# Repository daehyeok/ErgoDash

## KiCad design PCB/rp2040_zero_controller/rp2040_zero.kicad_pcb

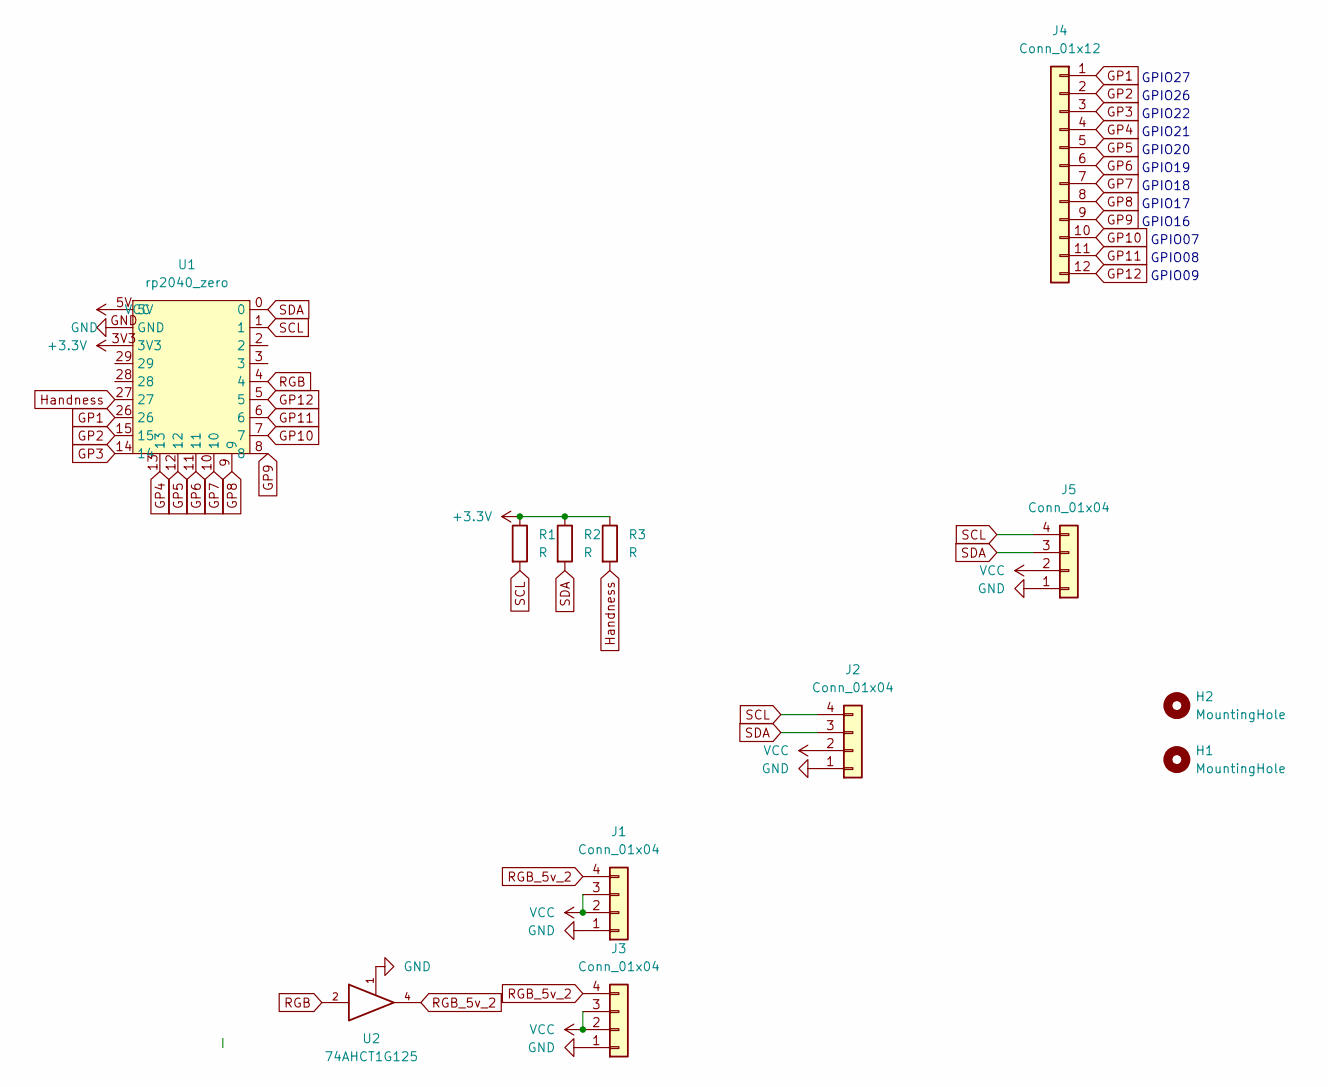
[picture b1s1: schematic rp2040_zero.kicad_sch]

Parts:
H1, H2: MountingHole; MountingHole_2.1mm
J1, J2, J3, J5: Conn_01x04; JST_SH_SM04B-SRSS-TB_1x04-1MP_P1.00mm_Horizontal
J4: Conn_01x12; Molex_200528-0120_1x12-1MP_P1.00mm_Horizontal
R1, R2, R3: R; R_1206_3216Metric_Pad1.30x1.75mm_HandSolder
U1: rp2040_zero; RPi_Pico_C
U2: 74AHCT1G125; SOT-23-5_HandSoldering

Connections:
+3V3: R1.1, R2.1, R3.1, U1.3V3
GND: J1.1, J2.1, J3.1, J5.1, U1.GND, U2.1, U2.3 (GND)
GP1: J4.1, U1.26
GP2: J4.2, U1.15
GP3: J4.3, U1.14
GP4: J4.4, U1.13
GP5: J4.5, U1.12
GP6: J4.6, U1.11
GP7: J4.7, U1.10
GP8: J4.8, U1.9
GP9: J4.9, U1.8
GP10: J4.10, U1.7
GP11: J4.11, U1.6
GP12: J4.12, U1.5
Handness: R3.2, U1.27
RGB: U1.4, U2.2
RGB_5v_2: J1.4, J3.4, U2.4
SCL: J2.4, J5.4, R1.2, U1.1
SDA: J2.3, J5.3, R2.2, U1.0
VCC: J1.2, J1.3, J2.2, J3.2, J3.3, J5.2, U1.5V, U2.5 (VCC)

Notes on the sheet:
GPIO27
GPIO08
GPIO22
GPIO18
GPIO21
GPIO20
GPIO17
GPIO16
GPIO26
GPIO19
GPIO07
GPIO09

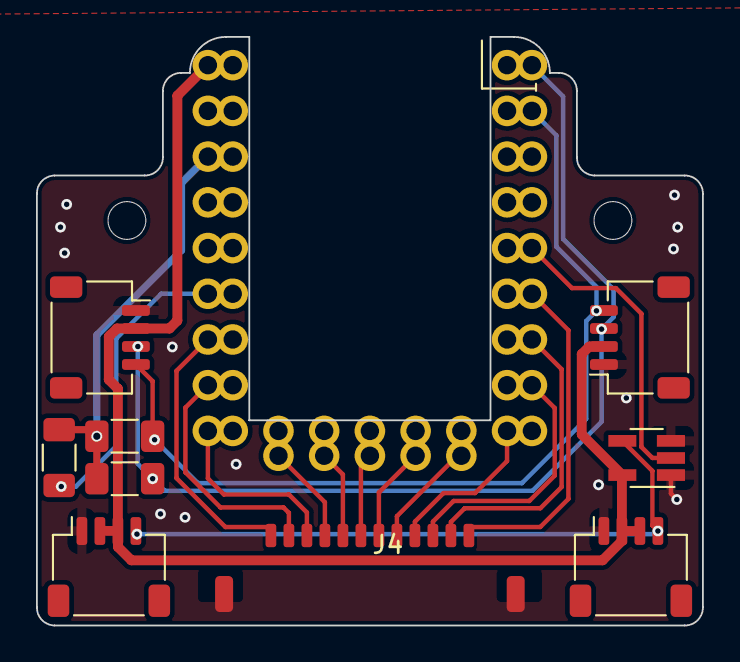
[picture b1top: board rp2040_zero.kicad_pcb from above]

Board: 2 copper layers, 37.0 x 32.7 mm, 12 parts (0 on the bottom side), 20 nets.

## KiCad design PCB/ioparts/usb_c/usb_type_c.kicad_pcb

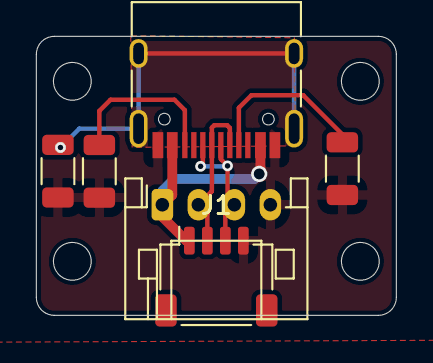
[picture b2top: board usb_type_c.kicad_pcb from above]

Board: 2 copper layers, 20.0 x 15.5 mm, 10 parts (0 on the bottom side), 7 nets.

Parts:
H1, H2, H3, H4: MountingHole; MountingHole_2.1mm
J1: Conn_01x04; JST_SH_SM04B-SRSS-TB_1x04-1MP_P1.00mm_Horizontal
J2: USB_C_Receptacle_USB2.0; USB_C_Receptacle_HRO_TYPE-C-31-M-12
J4: Conn_01x04; JST_PH_S4B-PH-K_1x04_P2.00mm_Horizontal
R1, R2: 5.1K; R_1206_3216Metric
R3: 0; R_1206_3216Metric

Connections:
DM_C: J1.2, J2.A7 (D-), J2.B7 (D-), J4.2
DP_C: J1.3, J2.A6 (D+), J2.B6 (D+), J4.3
GND: J1.4, J2.A1 (GND), J2.A12 (GND), J2.B1 (GND), J2.B12 (GND), J4.4, R1.2, R2.2, R3.2
unnamed: J2.A5 (CC1), R1.1
unnamed: J2.B5 (CC2), R2.1
SHIELD: J2.S1 (SHIELD), R3.1
VBUS_C: J1.1, J2.A4 (VBUS), J2.A9 (VBUS), J2.B4 (VBUS), J2.B9 (VBUS), J4.1

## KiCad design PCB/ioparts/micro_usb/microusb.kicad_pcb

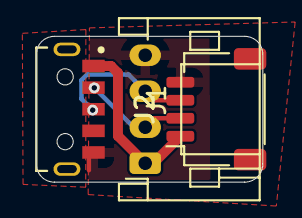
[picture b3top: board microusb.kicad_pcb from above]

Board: 2 copper layers, 12.6 x 8.1 mm, 3 parts (0 on the bottom side), 4 nets.

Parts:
J1: USB_B_Micro; HRO_U-G-M5WS-W-01
J2: Conn_01x04; JST_SH_SM04B-SRSS-TB_1x04-1MP_P1.00mm_Horizontal
J3: Conn_01x04; JST_PH_S4B-PH-K_1x04_P2.00mm_Horizontal

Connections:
DM_MICRO: J1.2 (D-), J2.2, J3.2
DP_MICRO: J1.3 (D+), J2.3, J3.3
GND1: J1.5 (GND), J2.4, J3.4
VBUS: J1.1 (VBUS), J2.1, J3.1

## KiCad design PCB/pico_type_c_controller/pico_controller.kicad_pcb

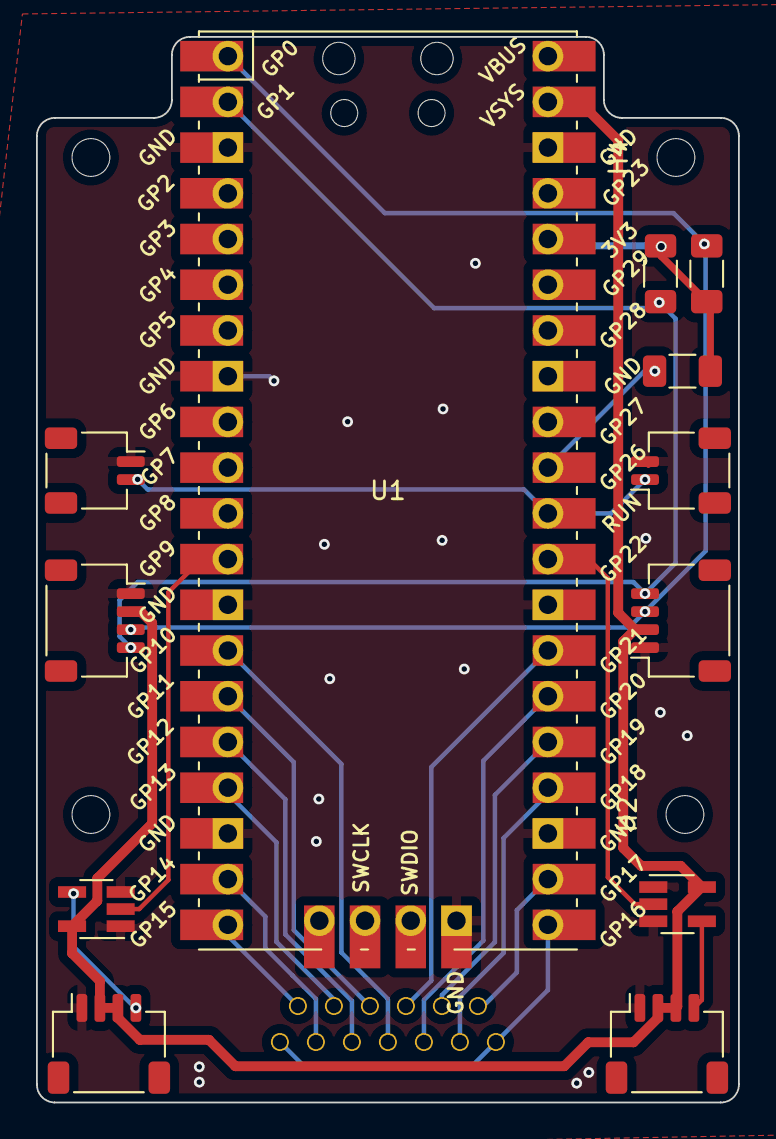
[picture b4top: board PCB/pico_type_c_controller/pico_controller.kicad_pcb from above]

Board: 2 copper layers, 39.0 x 59.2 mm, 17 parts (1 on the bottom side), 23 nets.

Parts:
H1, H2, H3, H4: MountingHole; MountingHole_2.1mm
J1, J2, J3, J5: Conn_01x04; JST_SH_SM04B-SRSS-TB_1x04-1MP_P1.00mm_Horizontal
J4: Conn_01x12; HDGC_1.0K-J-12PW
J6, J7: Conn_01x02; JST_SH_SM02B-SRSS-TB_1x02-1MP_P1.00mm_Horizontal
R1, R2, R3: R; R_1206_3216Metric_Pad1.30x1.75mm_HandSolder
U1: Pico; RPi_Pico_C
U2, U3: 74AHCT1G125; SOT-23-5_HandSoldering

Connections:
+3V3: R1.1, R2.1, R3.2, U1.36 (3V3)
GND: J1.1, J2.1, J3.1, J5.1, J6.2, J7.1, U1.3 (GND), U1.8 (GND), U1.13 (GND), U1.18 (GND), U1.23 (GND), U1.28 (GND), U1.38 (GND), U1.42 (GND), U2.1, U2.3 (GND), U3.1, U3.3 (GND)
GP1: J4.1, U1.20 (GPIO15)
GP2: J4.2, U1.19 (GPIO14)
GP3: J4.3, U1.17 (GPIO13)
GP4: J4.4, U1.16 (GPIO12)
GP5: J4.5, U1.15 (GPIO11)
GP6: J4.6, U1.14 (GPIO10)
GP7: J4.7, U1.27 (GPIO21)
GP8: J4.8, U1.26 (GPIO20)
GP9: J4.9, U1.25 (GPIO19)
GP10: J4.10, U1.24 (GPIO18)
GP11: J4.11, U1.22 (GPIO17)
GP12: J4.12, U1.21 (GPIO16)
Handness: R3.1, U1.31 (GPIO26_ADC0)
RGB: U1.29 (GPIO22), U3.2
RGB2: U1.12 (GPIO9), U2.2
RGB_5v: J2.4, U3.4
RGB_5v_2: J3.4, U2.4
RUN: J6.1, J7.2, U1.30 (RUN)
SCL: J1.4, J5.4, R2.2, U1.2 (GPIO1)
SDA: J1.3, J5.3, R1.2, U1.1 (GPIO0)
VCC: J1.2, J2.2, J2.3, J3.2, J3.3, J5.2, U1.39 (VSYS), U2.5 (VCC), U3.5 (VCC)

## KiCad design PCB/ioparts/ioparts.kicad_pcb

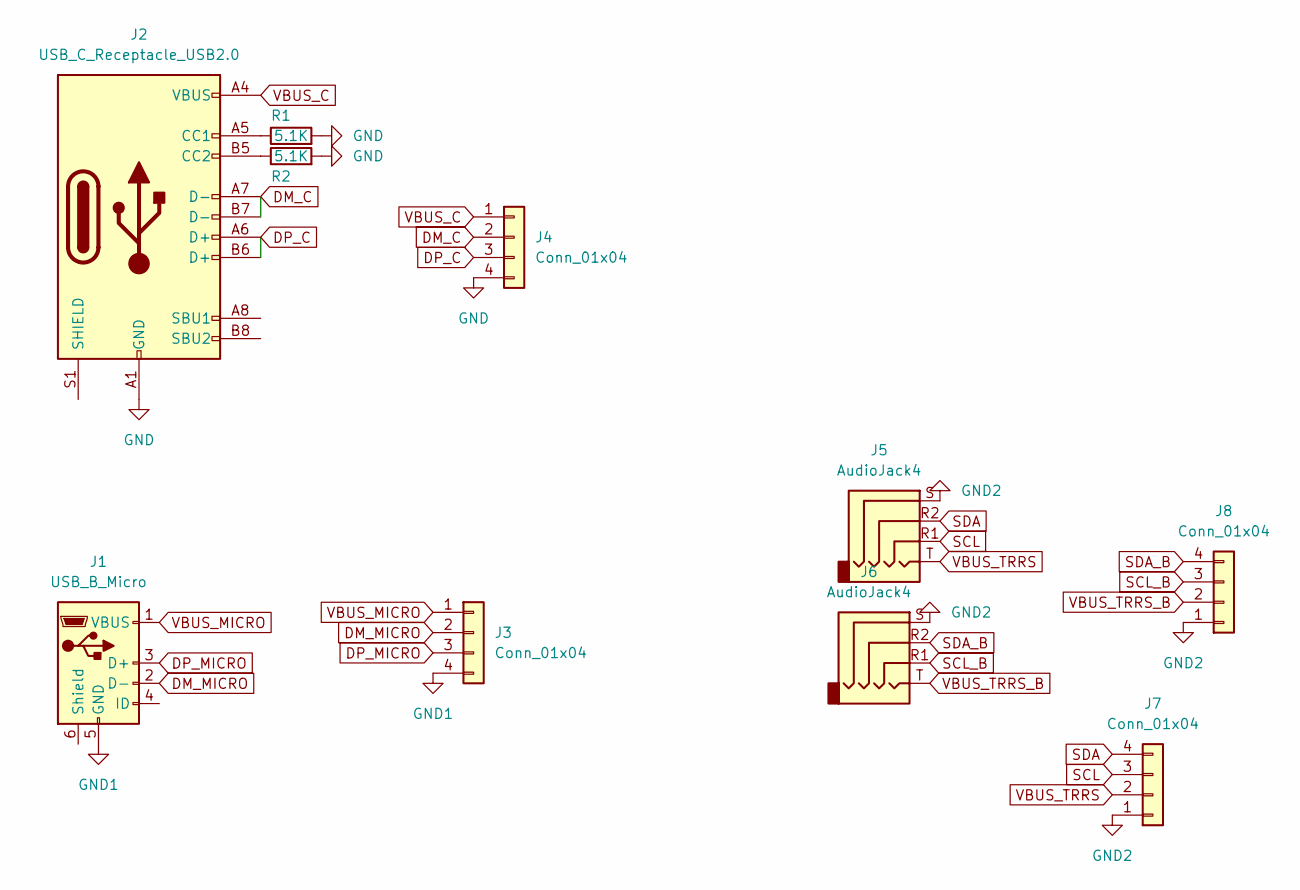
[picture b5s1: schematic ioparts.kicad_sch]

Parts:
J1: USB_B_Micro; HRO_U-G-M5WS-W-01
J2: USB_C_Receptacle_USB2.0; USB_C_Receptacle_HRO_TYPE-C-31-M-12
J3, J4: Conn_01x04; JST_PH_S4B-PH-K_1x04_P2.00mm_Horizontal
J5, J6: AudioJack4; Jack_3.5mm_PJ320D_Horizontal
J7, J8: Conn_01x04; JST_SH_SM04B-SRSS-TB_1x04-1MP_P1.00mm_Horizontal
R1, R2: 5.1K; R_1206_3216Metric

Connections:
DM_C: J2.A7 (D-), J2.B7 (D-), J4.2
DM_MICRO: J1.2 (D-), J3.2
DP_C: J2.A6 (D+), J2.B6 (D+), J4.3
DP_MICRO: J1.3 (D+), J3.3
GND: J2.A1 (GND), J2.A12 (GND), J2.B1 (GND), J2.B12 (GND), J4.4, R1.2, R2.2
GND1: J1.5 (GND), J3.4
GND2: J5.S, J6.S, J7.1, J8.1
unnamed: J2.A5 (CC1), R1.1
unnamed: J2.B5 (CC2), R2.1
SCL: J5.R1, J7.3
SCL_B: J6.R1, J8.3
SDA: J5.R2, J7.4
SDA_B: J6.R2, J8.4
VBUS_C: J2.A4 (VBUS), J2.A9 (VBUS), J2.B4 (VBUS), J2.B9 (VBUS), J4.1
VBUS_MICRO: J1.1 (VBUS), J3.1
VBUS_TRRS: J5.T, J7.2
VBUS_TRRS_B: J6.T, J8.2

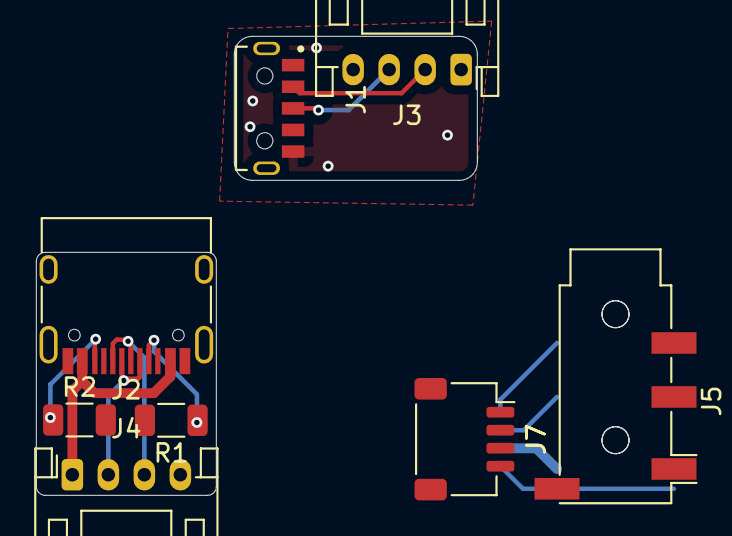
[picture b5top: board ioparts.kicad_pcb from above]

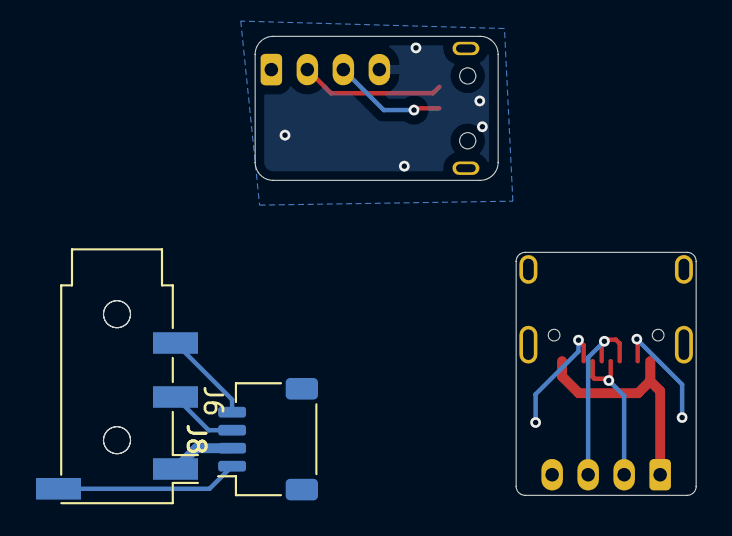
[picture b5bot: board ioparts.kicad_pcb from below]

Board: 2 copper layers, 24.5 x 25.5 mm, 10 parts (2 on the bottom side), 17 nets.

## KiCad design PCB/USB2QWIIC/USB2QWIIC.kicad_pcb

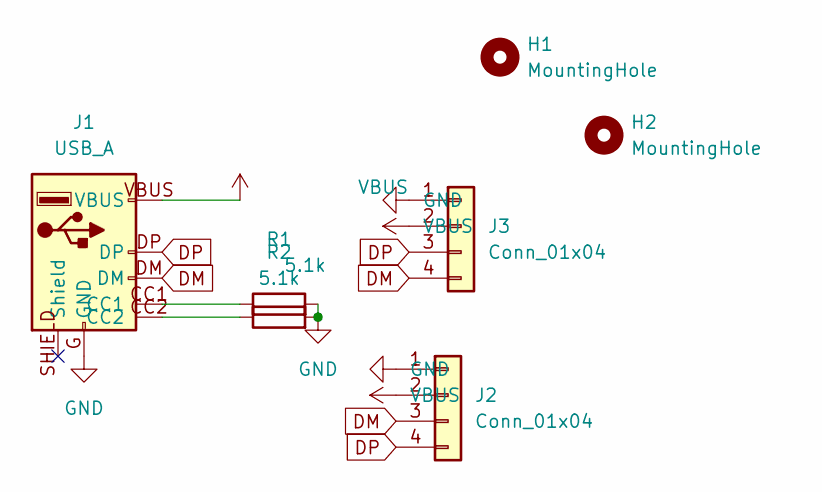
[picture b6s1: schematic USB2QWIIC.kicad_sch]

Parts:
H1, H2: MountingHole; MountingHole_2.2mm_M2
J1: USB_A; KH-TYPE-C-L10-14P
J2, J3: Conn_01x04; JST_SH_BM04B-SRSS-TB_1x04-1MP_P1.00mm_Vertical
R1, R2: 5.1k; R_1206_3216Metric_Pad1.30x1.75mm_HandSolder

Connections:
DM: J1.DM, J2.3, J3.4
DP: J1.DP, J2.4, J3.3
GND: J1.G (GND), J2.1, J3.1, R1.2, R2.2
unnamed: J1.CC1, R1.1
unnamed: J1.CC2, R2.1
VBUS: J1.VBUS, J2.2, J3.2

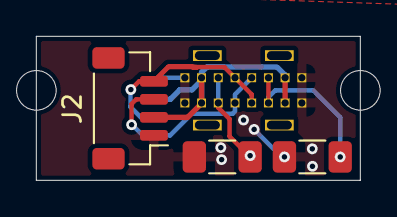
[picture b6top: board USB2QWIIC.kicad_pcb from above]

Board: 2 copper layers, 18.0 x 8.0 mm, 7 parts (1 on the bottom side), 6 nets.

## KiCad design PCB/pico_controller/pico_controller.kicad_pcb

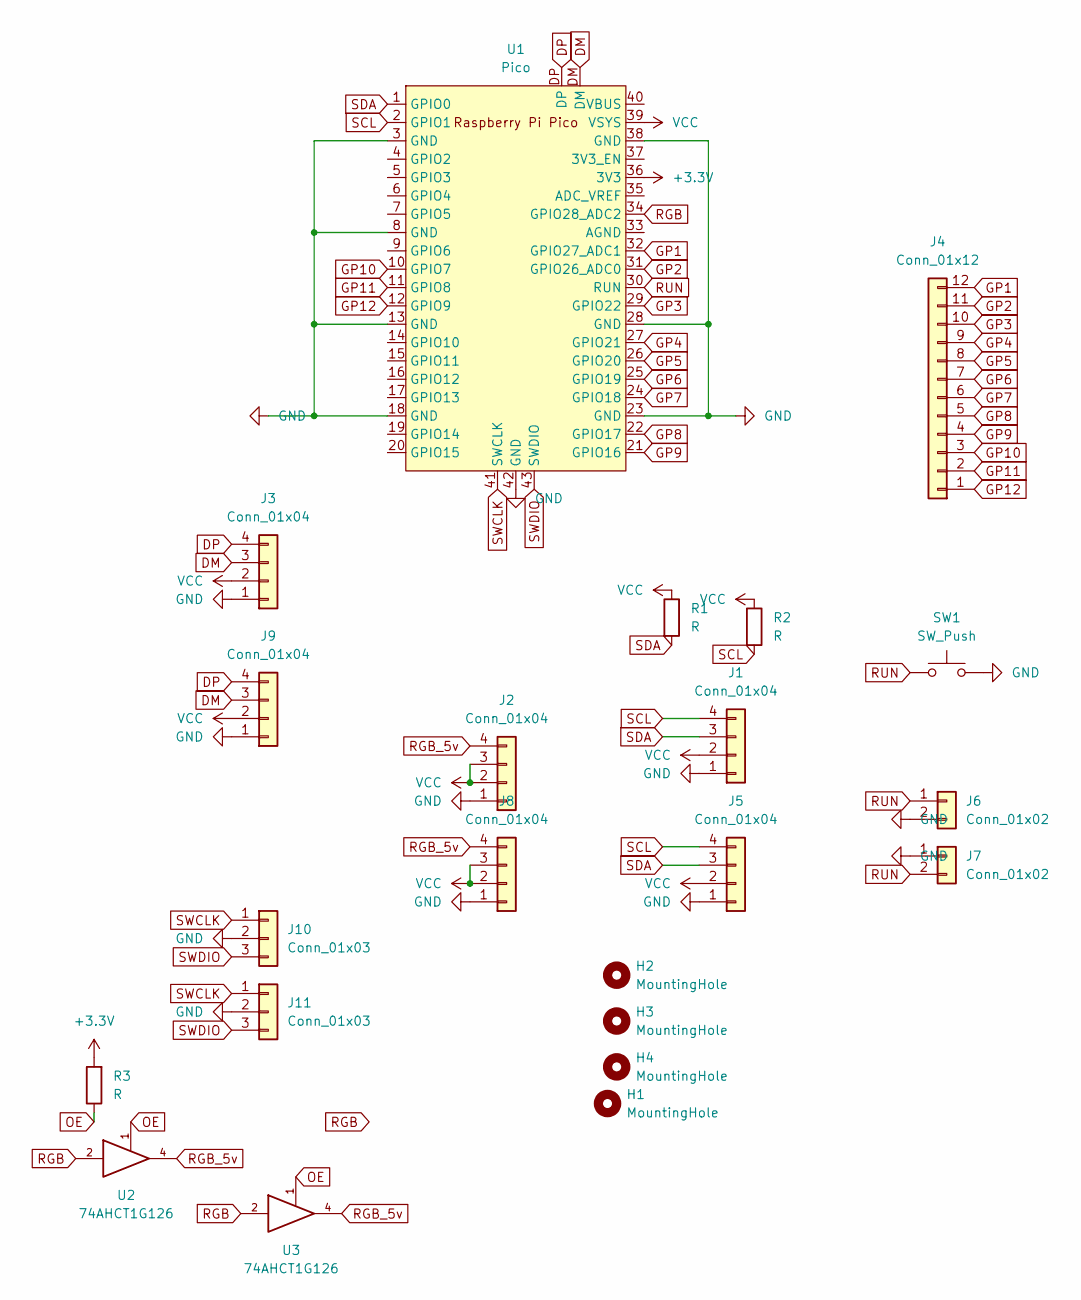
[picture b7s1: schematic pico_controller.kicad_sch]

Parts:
H1, H2, H3, H4: MountingHole; MountingHole_2.1mm
J1, J2, J3, J5, J8, J9: Conn_01x04; JST_SH_SM04B-SRSS-TB_1x04-1MP_P1.00mm_Horizontal
J4: Conn_01x12; HDGC_1.0K-J-12PW
J6, J7: Conn_01x02; JST_SHL_SM02B-SHLS-TF_1x02-1MP_P1.00mm_Horizontal
J10, J11: Conn_01x03; JST_SH_SM03B-SRSS-TB_1x03-1MP_P1.00mm_Horizontal
R1, R2: R; R_0805_2012Metric_Pad1.20x1.40mm_HandSolder
R3: R; R_0805_2012Metric_Pad1.20x1.40mm_HandSolder_reversible
SW1: SW_Push; SW_PUSH_6mm
U1: Pico; RPi_Pico_SMD_TH
U2, U3: 74AHCT1G126; SOT-23-5_HandSoldering

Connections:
+3V3: R3.2, U1.36 (3V3)
DM: J3.3, J9.3, U1.DM
DP: J3.4, J9.4, U1.DP
GND: J1.1, J2.1, J3.1, J5.1, J6.2, J7.1, J8.1, J9.1, J10.2, J11.2, SW1.2, U1.3 (GND), U1.8 (GND), U1.13 (GND), U1.18 (GND), U1.23 (GND), U1.28 (GND), U1.38 (GND), U1.42 (GND), U2.3 (GND), U3.3 (GND)
GP1: J4.12, U1.32 (GPIO27_ADC1)
GP2: J4.11, U1.31 (GPIO26_ADC0)
GP3: J4.10, U1.29 (GPIO22)
GP4: J4.9, U1.27 (GPIO21)
GP5: J4.8, U1.26 (GPIO20)
GP6: J4.7, U1.25 (GPIO19)
GP7: J4.6, U1.24 (GPIO18)
GP8: J4.5, U1.22 (GPIO17)
GP9: J4.4, U1.21 (GPIO16)
GP10: J4.3, U1.10 (GPIO7)
GP11: J4.2, U1.11 (GPIO8)
GP12: J4.1, U1.12 (GPIO9)
Handness: U1.9 (GPIO6); also elsewhere on the board
OE: R3.1, U2.1, U3.1; also elsewhere on the board
RGB: U1.34 (GPIO28_ADC2), U2.2, U3.2
RGB_5v: J2.4, J8.4, U2.4, U3.4
RUN: J6.1, J7.2, SW1.1, U1.30 (RUN)
SCL: J1.4, J5.4, R2.2, U1.2 (GPIO1)
SDA: J1.3, J5.3, R1.2, U1.1 (GPIO0)
SWCLK: J10.1, J11.1, U1.41 (SWCLK)
SWDIO: J10.3, J11.3, U1.43 (SWDIO)
VCC: J1.2, J2.2, J2.3, J3.2, J5.2, J8.2, J8.3, J9.2, R1.1, R2.1, U1.39 (VSYS), U2.5 (VCC), U3.5 (VCC)

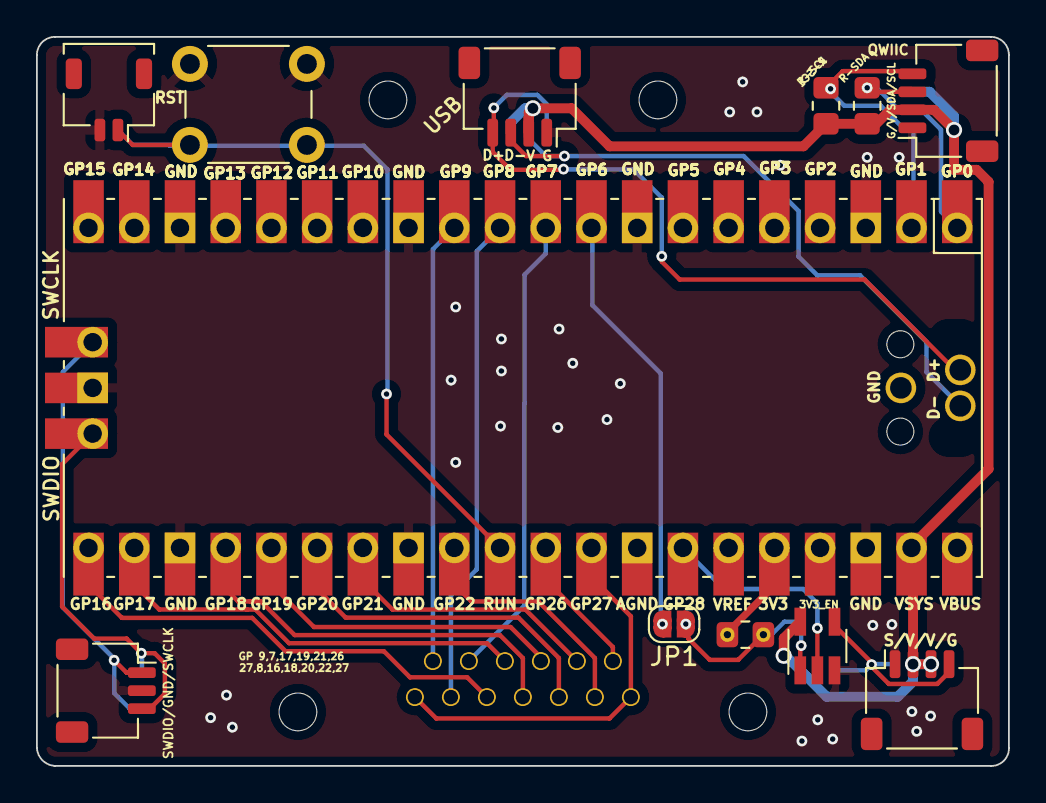
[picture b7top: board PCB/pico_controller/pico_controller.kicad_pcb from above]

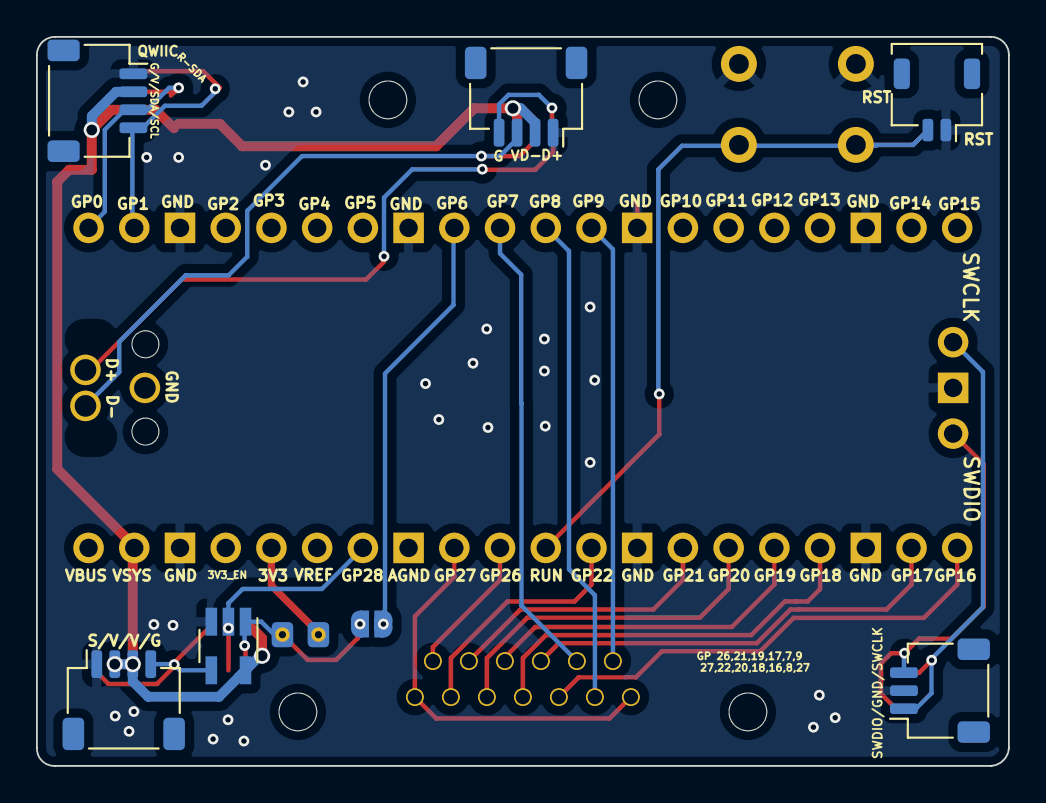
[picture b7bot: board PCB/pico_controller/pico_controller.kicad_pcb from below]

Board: 2 copper layers, 54.0 x 40.5 mm, 23 parts (7 on the bottom side), 26 nets.

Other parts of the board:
JP1: Jumper_2_Bridged; SolderJumper-2_P1.3mm_Open_RoundedPad1.0x1.5mm

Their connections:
Handness: JP1.2 (B); also elsewhere on the board
OE: JP1.1 (A); also elsewhere on the board

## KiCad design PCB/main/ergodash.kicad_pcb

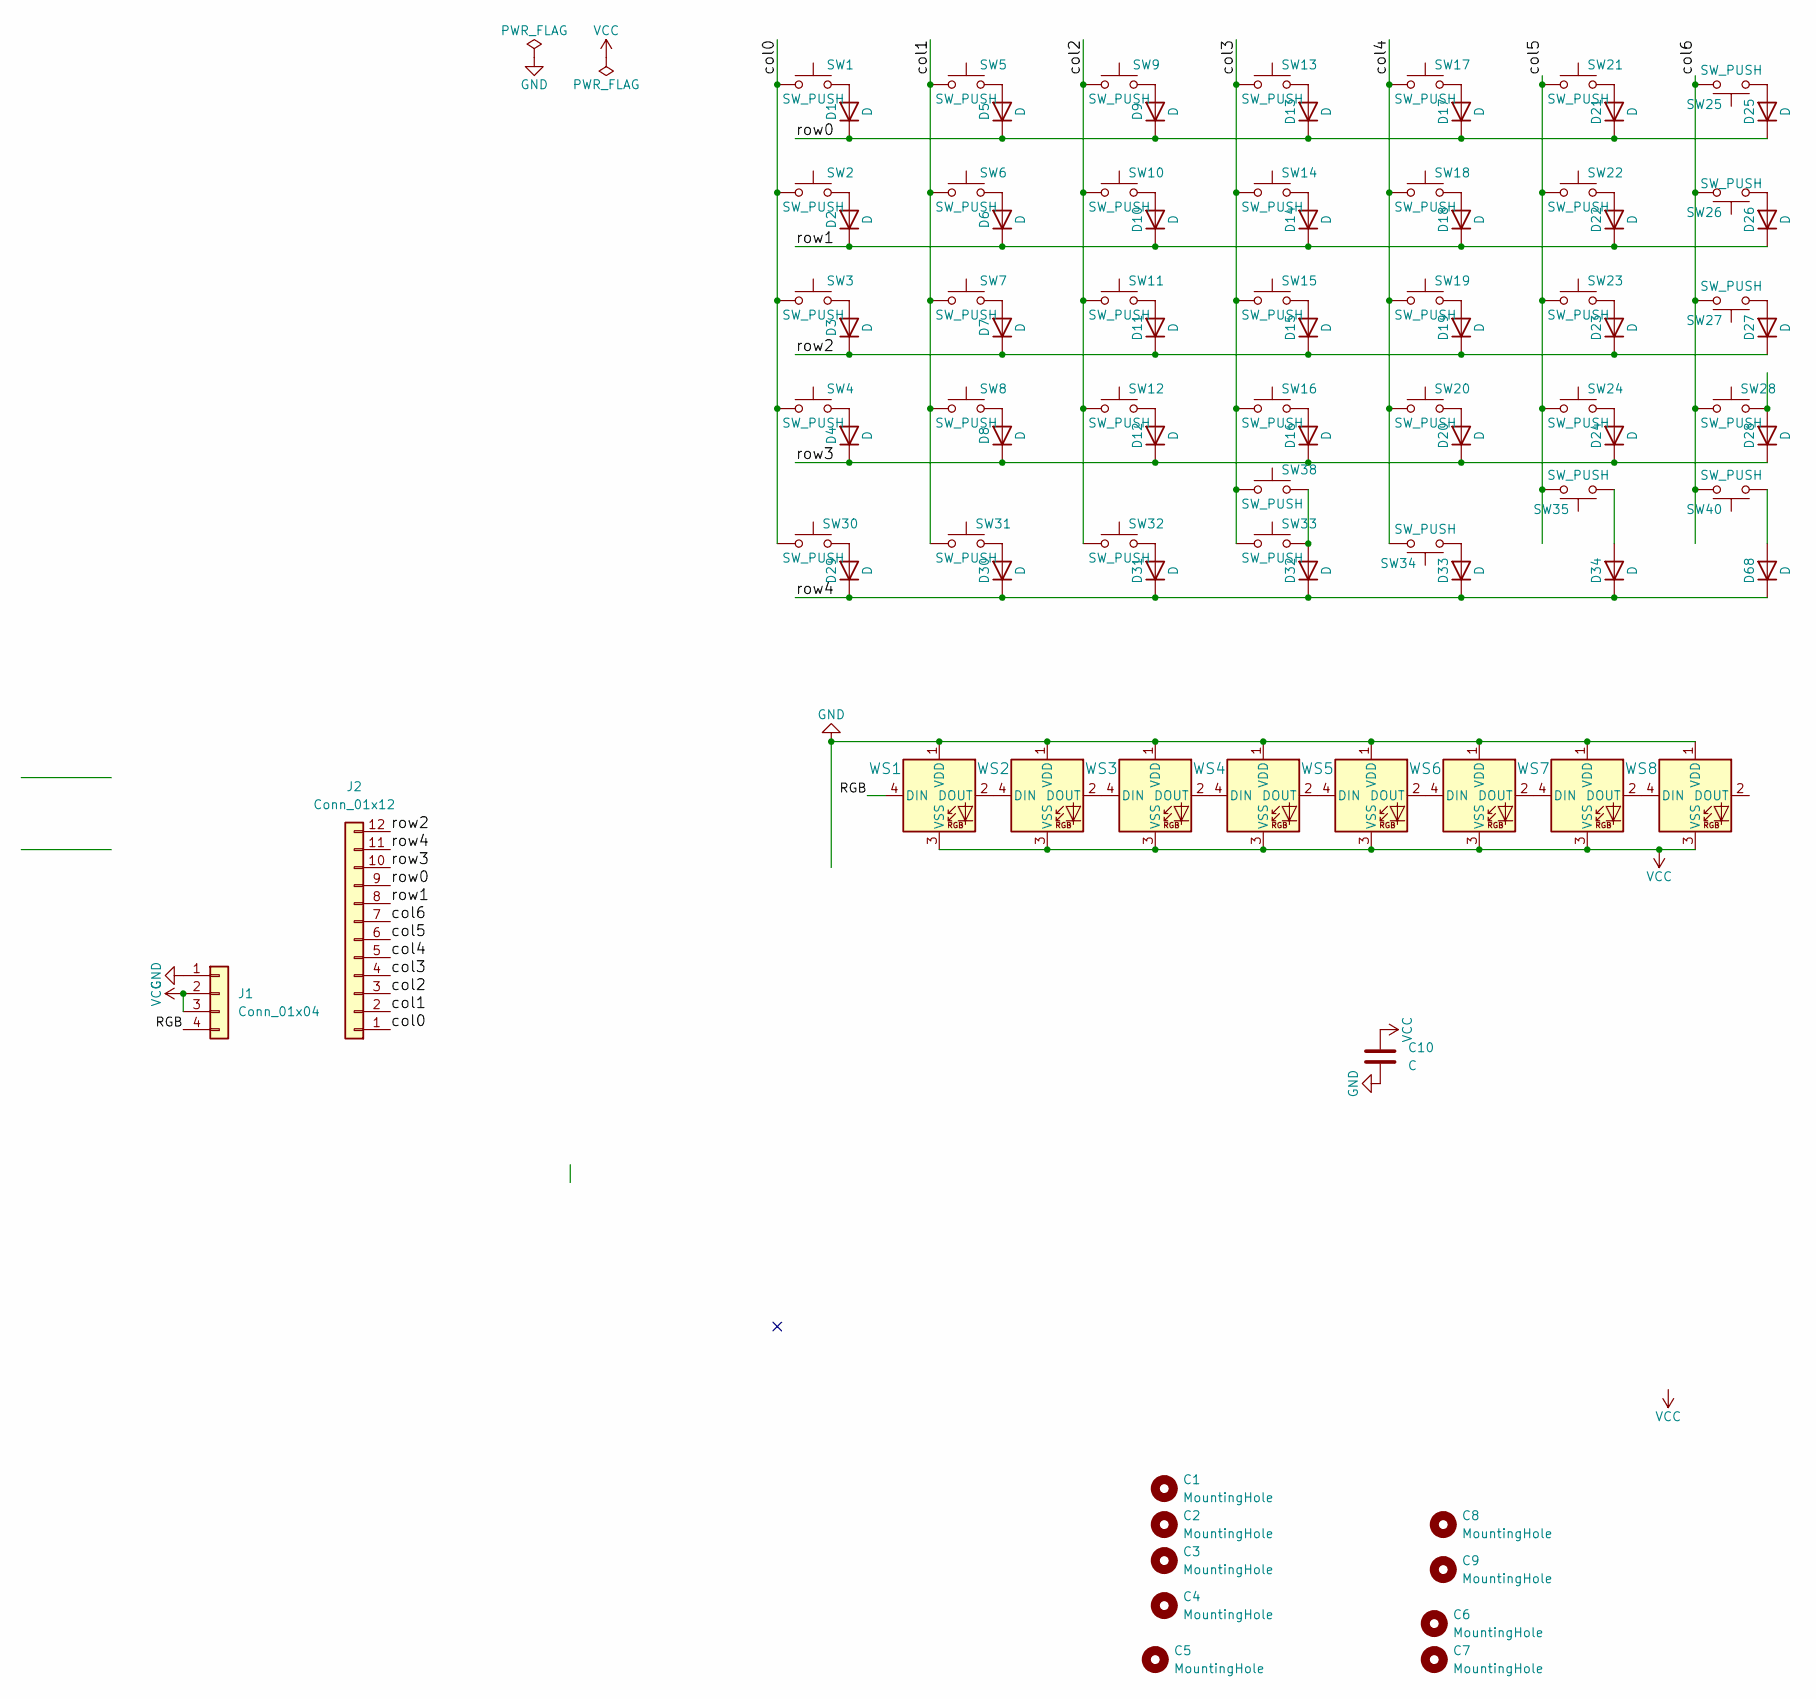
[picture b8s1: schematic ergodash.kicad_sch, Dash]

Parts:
C1, C2, C3, C4, C5, C6, C7, C8, C9: MountingHole; Plate_MountingHole_cut
C10: C; C_1206_3216Metric
D1, D2, D3, D4, D5, D6, D7, D8, D9, D10, D11, D12, D13, D14, D15, D16, D17, D18, D19, D20, D21, D22, D23, D24, D25, D26, D27, D28, D29, D30, D31, D32, D33, D34, D68: D; D_SOD-123-dobuleside
J1: Conn_01x04; JST_SH_SM04B-SRSS-TB_1x04-1MP_P1.00mm_Horizontal
J2: Conn_01x12; HDGC_1.0K-J-12PW
SW1, SW2, SW3, SW4, SW30: SW_PUSH; Kailh_socket_MX_leftmost
SW5, SW6, SW7, SW8, SW9, SW10, SW11, SW12, SW13, SW14, SW15, SW16, SW17, SW18, SW19, SW20, SW21, SW22, SW23, SW24, SW28, SW31, SW32, SW33, SW34, SW35, SW38, SW40: SW_PUSH; Kailh_socket_MX
SW25, SW26, SW27: SW_PUSH; Kailh_socket_MX_rightmost
WS1, WS2, WS3, WS4, WS5, WS6, WS7, WS8: WS2812B; LED_WS2812B_reversible

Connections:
/RGB: J1.4, WS1.4 (DIN)
/col0: J2.1, SW1.1, SW2.1, SW3.1, SW4.1, SW30.1
/col1: J2.2, SW5.1, SW6.1, SW7.1, SW8.1, SW31.1
/col2: J2.3, SW9.1, SW10.1, SW11.1, SW12.1, SW32.1
/col3: J2.4, SW13.1, SW14.1, SW15.1, SW16.1, SW33.1, SW38.1
/col4: J2.5, SW17.1, SW18.1, SW19.1, SW20.1, SW34.2
/col5: J2.6, SW21.1, SW22.1, SW23.1, SW24.1, SW35.2
/col6: J2.7, SW25.2, SW26.2, SW27.2, SW28.1, SW40.2
/row0: D1.1 (K), D5.1 (K), D9.1 (K), D13.1 (K), D17.1 (K), D21.1 (K), D25.1 (K), J2.9
/row1: D2.1 (K), D6.1 (K), D10.1 (K), D14.1 (K), D18.1 (K), D22.1 (K), D26.1 (K), J2.8
/row2: D3.1 (K), D7.1 (K), D11.1 (K), D15.1 (K), D19.1 (K), D23.1 (K), D27.1 (K), J2.12
/row3: D4.1 (K), D8.1 (K), D12.1 (K), D16.1 (K), D20.1 (K), D24.1 (K), D28.1 (K), J2.10
/row4: D29.1 (K), D30.1 (K), D31.1 (K), D32.1 (K), D33.1 (K), D34.1 (K), D68.1 (K), J2.11
GND: C10.2, J1.1, WS1.1 (VDD), WS2.1 (VDD), WS3.1 (VDD), WS4.1 (VDD), WS5.1 (VDD), WS6.1 (VDD), WS7.1 (VDD), WS8.1 (VDD)
unnamed: D1.2 (A), SW1.2
unnamed: D2.2 (A), SW2.2
unnamed: D3.2 (A), SW3.2
unnamed: D4.2 (A), SW4.2
unnamed: D5.2 (A), SW5.2
unnamed: D6.2 (A), SW6.2
unnamed: D7.2 (A), SW7.2
unnamed: D8.2 (A), SW8.2
unnamed: D9.2 (A), SW9.2
unnamed: D10.2 (A), SW10.2
unnamed: D11.2 (A), SW11.2
unnamed: D12.2 (A), SW12.2
unnamed: D13.2 (A), SW13.2
unnamed: D14.2 (A), SW14.2
unnamed: D15.2 (A), SW15.2
unnamed: D16.2 (A), SW16.2
unnamed: D17.2 (A), SW17.2
unnamed: D18.2 (A), SW18.2
unnamed: D19.2 (A), SW19.2
unnamed: D20.2 (A), SW20.2
unnamed: D21.2 (A), SW21.2
unnamed: D22.2 (A), SW22.2
unnamed: D23.2 (A), SW23.2
unnamed: D24.2 (A), SW24.2
unnamed: D25.2 (A), SW25.1
unnamed: D26.2 (A), SW26.1
unnamed: D27.2 (A), SW27.1
unnamed: D28.2 (A), SW28.2
unnamed: D29.2 (A), SW30.2
unnamed: D30.2 (A), SW31.2
unnamed: D31.2 (A), SW32.2
unnamed: D32.2 (A), SW33.2, SW38.2
unnamed: D33.2 (A), SW34.1
unnamed: D34.2 (A), SW35.1
unnamed: D68.2 (A), SW40.1
unnamed: WS1.2 (DOUT), WS2.4 (DIN)
unnamed: WS2.2 (DOUT), WS3.4 (DIN)
unnamed: WS4.2 (DOUT), WS5.4 (DIN)
unnamed: WS3.2 (DOUT), WS4.4 (DIN)
unnamed: WS5.2 (DOUT), WS6.4 (DIN)
unnamed: WS6.2 (DOUT), WS7.4 (DIN)
unnamed: WS7.2 (DOUT), WS8.4 (DIN)
VCC: C10.1, J1.2, J1.3, WS1.3 (VSS), WS2.3 (VSS), WS3.3 (VSS), WS4.3 (VSS), WS5.3 (VSS), WS6.3 (VSS), WS7.3 (VSS), WS8.3 (VSS)

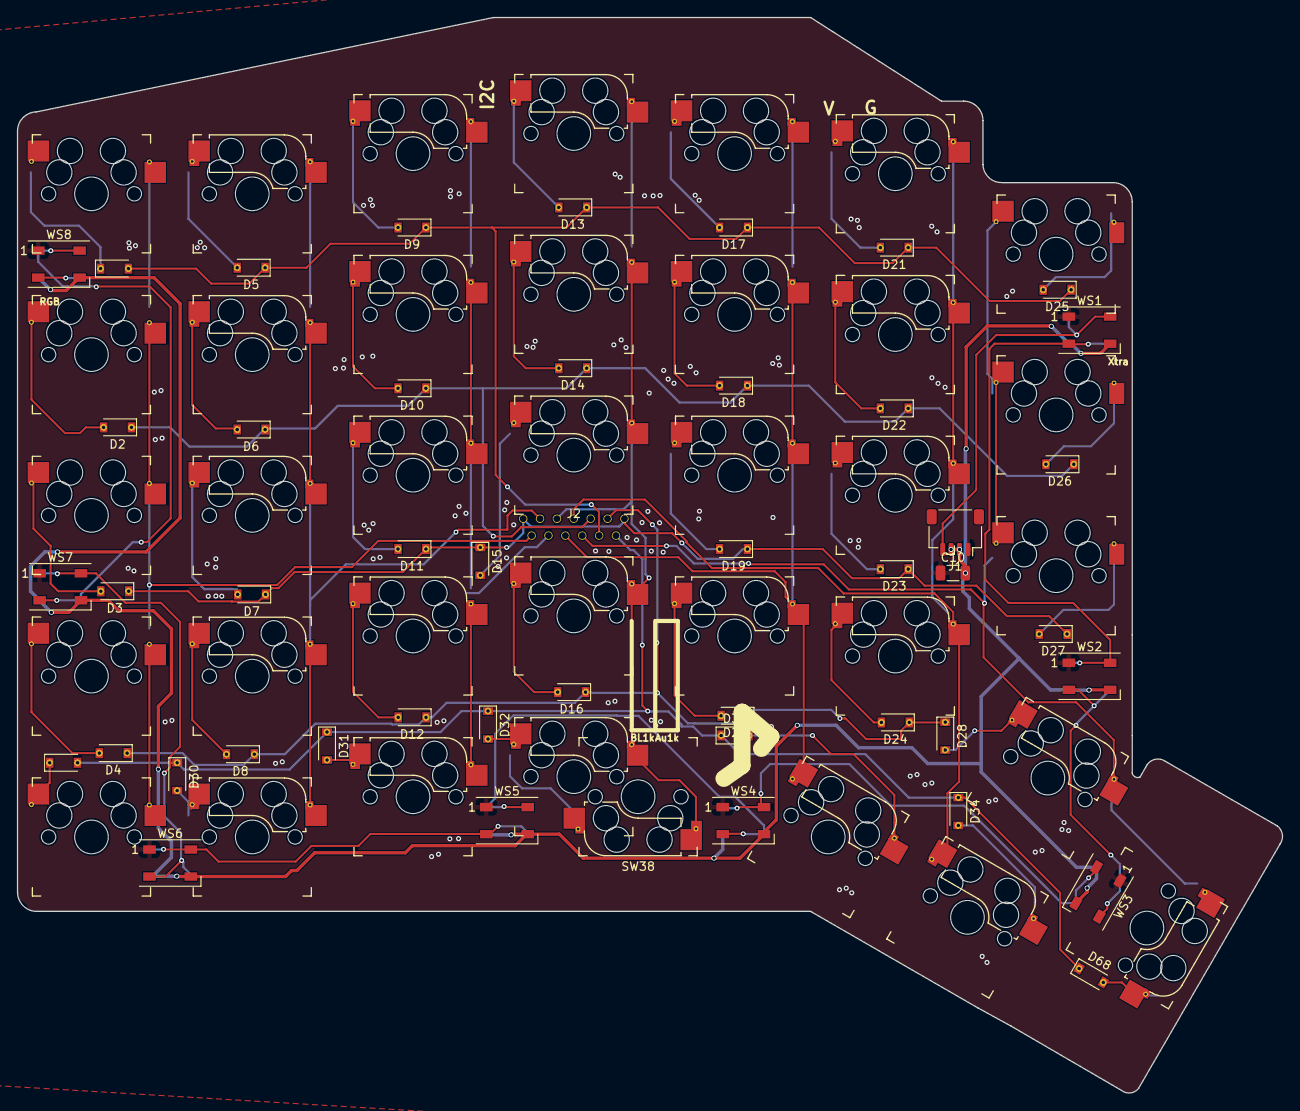
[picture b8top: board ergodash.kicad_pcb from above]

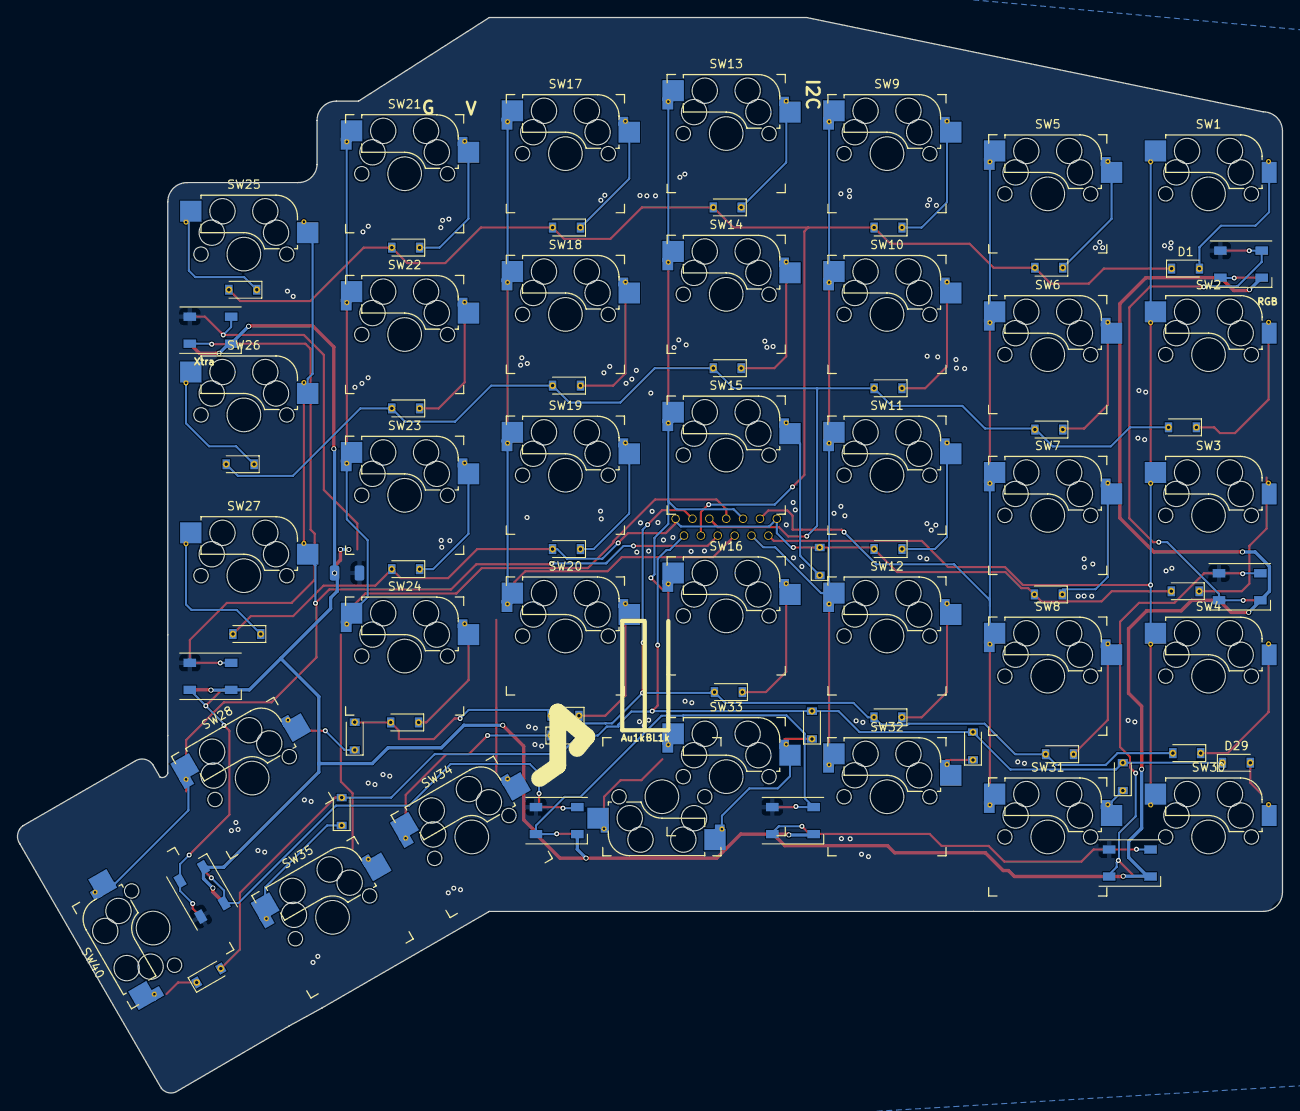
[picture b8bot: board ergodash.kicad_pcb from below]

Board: 2 copper layers, 149.9 x 127.4 mm, 82 parts (3 on the bottom side), 57 nets.

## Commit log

2022-06-05 fork & clean up files
2022-06-05 temp
2022-06-09 initial RP Pico controoler board
2022-06-09 add handness jumper to controller
2022-06-10 without led
2022-06-10 before cut
2022-06-12 simpler version
2022-06-13 openscad case init
2022-06-13 Fix dxf files
2022-06-13 init of case
2022-06-18 usb mount board
2022-07-04 firmware init
2022-07-08 pico_type_c_controoler
2022-07-08 misc pcbs
2022-07-15 firwmare tap layout
2022-07-25 firmware temp
